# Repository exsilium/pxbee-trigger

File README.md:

# pxbee-trigger

Programmable XBee Trigger that is ZigBee Home Automation profile compliant. Possible to integrate with [SmartThings](https://www.smartthings.com) Hub v3 or a separate ZigBee / XBee network. Includes a reference hardware design up to 4 channels with a full BOM, perfect for DIYselfers out there.

Used in real life to automate garage / gate automatons.

## Hardware example

An assembled board without a mounted XBee radio. Metric scale for reference (cm.). Board dimension - 51 x 57 mm.
## Bill of Materials (BOM)

| Designator  | Component                                                                                                            | Manufacturer                                      | Quantity | SKU / Part nr.                | Spec                                                                               | Option |
| ----------- | -------------------------------------------------------------------------------------------------------------------- | ------------------------------------------------- | -------- | ----------------------------- | ---------------------------------------------------------------------------------- | ------ |
| XB1         | [Programmable XBee](https://www.digi.com/products/xbee-rf-solutions/rf-modules/xbee-zigbee#partnumbers) (with RPSMA) | [Digi](https://www.digi.com)                      |        1 | XBP24CZ7SITB003               | [PDF](http://www.digi.com/resources/documentation/digidocs/pdfs/90002002.pdf)      |        |
| BR1         | [Bridge Rectifier DF01M](https://www.mouser.ee/ProductDetail/512-DF01M)                                              | [ON Semiconductor](https://www.onsemi.com)        |        1 | Mouser No: 512-DF01M          | [PDF](https://www.mouser.ee/datasheet/2/308/DF10M-D-1803766.pdf)                   |        |
| C1 (C2)     | [Electrolytic Capacitor - Radial 220uF 50V](https://www.mouser.ee/ProductDetail/EEU-FM1H221)                         | [Panasonic](https://industrial.panasonic.com).    |      1-2 | Mouser No: 667-EEU-FM1H221.   | [PDF](https://www.mouser.ee/datasheet/2/315/ABA0000C1018-947496.pdf).              |        |
| PS1         | [DC/DC Isolated Converter Cosel MGFS1R5243R3](https://www.mouser.ee/ProductDetail/436-MGFS1R5243R3)                  | [Cosel](https://www.coseleurope.eu)               |        1 | Mouser No: 436-MGFS1R5243R3   | [PDF](https://www.mouser.ee/datasheet/2/622/SFE_MGFS-1115632.pdf)                  |        |
| Q1,Q2,Q3,Q4 | [Bipolar Transistor BC548BTA](https://www.mouser.ee/ProductDetail/512-BC548BTA)                                      | [ON Semiconductor](https://www.onsemi.com)        |        4 | Mouser No: 512-BC548BTA       | [PDF](https://www.mouser.ee/datasheet/2/308/BC548-1118644.pdf)                     |        |
| D1,D2,D3,D4 | [Diode 1N4004](https://www.mouser.ee/ProductDetail/863-1N4004RLG)                                                    | [ON Semiconductor](https://www.onsemi.com)        |        4 | Mouser No: 863-1N4004RLG      | [PDF](https://www.mouser.ee/datasheet/2/308/1N4001-D-110363.pdf)                   |        |
| K1,K2,K3,K4 | [General Purpose Relay (APAN3103)](https://www.mouser.ee/ProductDetail/769-APAN3103)                                 | [Panasonic](https://industrial.panasonic.com)     |        4 | Mouser No: 769-APAN3103       | [PDF](https://www.mouser.ee/datasheet/2/315/mech_eng_pan-1299258.pdf)              |        |
| R1,R2,R3,R4 | [Resistor RN55D1801FB14](https://www.mouser.ee/ProductDetail/71-RN55D1801FB14)                                       | [Vishay](https://www.vishay.com)                  |        4 | Mouser No: 71-RN55D1801FB14   | [PDF](https://www.mouser.ee/datasheet/2/427/cmfmil-109690.pdf)                     |        |
| XB1         | [10 pin header for XBee](https://www.mouser.ee/ProductDetail/855-M22-7131042)                                        | [Harwin](https://www.harwin.com)                  |        2 | Mouser No: 855-M22-7131042    | [PDF](https://www.mouser.ee/datasheet/2/181/M22-713-1134021.pdf)                   |        |
| J1          | [2 pin Terminal Block (PCB)](https://www.mouser.ee/ProductDetail/538-39501-1002)                                     | [Molex](https://www.molex.com)                    |        1 | Mouser No: 538-39501-1002     | [PDF](https://www.mouser.ee/datasheet/2/276/0395011002_TERMINAL_BLOCKS-163759.pdf) | A      |
|             | [2 pin Terminal Plug](https://www.mouser.ee/ProductDetail/538-39500-0002)                                            | [Molex](https://www.molex.com)                    |        1 | Mouser No: 538-39500-0002     | [PDF](https://www.mouser.ee/datasheet/2/276/0395000002_TERMINAL_BLOCKS-136229.pdf) | A      |
| J2          | [9 pin Terminal Block (PCB)](https://www.mouser.ee/ProductDetail/538-39501-1009)                                     | [Molex](https://www.molex.com)                    |        1 | Mouser No: 538-39501-1009     | [PDF](https://www.mouser.ee/datasheet/2/276/0395011009_TERMINAL_BLOCKS-163629.pdf) | A      |
|             | [9 pin Terminal Plug](https://www.mouser.ee/ProductDetail/651-1908101)                                               | [Molex](https://www.molex.com)                    |        1 | Mouser No: 651-1908101        | [PDF](https://www.mouser.ee/datasheet/2/276/0395000009_TERMINAL_BLOCKS-163669.pdf) | A      |
| J1          | [2 pin Fixed Terminal Block (PCB)](https://www.mouser.ee/ProductDetail/538-39357-0002)                               | [Molex](https://www.molex.com)                    |        1 | Mouser No: 538-39357-0002     | [PDF](https://www.mouser.ee/datasheet/2/276/0393570002_TERMINAL_BLOCKS-227759.pdf) | B      |
| J2          | [9 pin Fixed Terminal Block (PCB)](https://www.mouser.ee/ProductDetail/538-39357-0009)                               | [Molex](https://www.molex.com)                    |        1 | Mouser No: 538-39357-0009     | [PDF](https://www.mouser.ee/datasheet/2/276/0393570009_TERMINAL_BLOCKS-136250.pdf) | B      |
|             | [Antenna with RP-SMA Connector](https://www.mouser.ee/ProductDetail/712-ANT-2.4-CW-RAH)                              | [Linx Technologies](https://linxtechnologies.com) |        1 | Mouser No: 712-ANT-2.4-CW-RAH | [PDF](https://www.mouser.ee/datasheet/2/238/ant-2.4-cw-rah-ccc-1659143.pdf)        |        |
| JP1         | [6 pin Debug Header](https://www.mouser.ee/ProductDetail/538-22-28-8065)                                             | [Molex](https://www.molex.com)                    |        1 | Mouser No: 538-22-28-8065     | [PDF](https://www.mouser.ee/datasheet/2/276/0022288065_PCB_HEADERS-159204.pdf)     | O      |
| J3          | [2 pin Reset Header](https://www.mouser.ee/ProductDetail/Molex/22-28-5027)                                           | [Molex](https://www.molex.com)                    |        1 | Mouser No: 538-22-28-5027     | [PDF](https://www.mouser.ee/ProductDetail/Molex/22-28-5027)                        | O      |

Standard 3.5 width headers are used. Option **A**) uses pluggable termination; **B**) Fixed screw termination; **O**) Parts are optional and meant for development; Components can easily be switched with other termination blocks or use direct wire soldering.

## Compiling

- On 32bit Linux target, simply: `make`
- On 64bit Linux target:
    - Intall 32bit compatible libraries: `sudo apt-get install lib32stdc++6`
    - `make`
- On MacOS:
    - Install [Docker](https://www.docker.com)
    - `make builddocker`
    - `make dall`

## Firmware

- Output file: `obj/trigger.abs.bin`
- Upload the file via local XMODEM or use Over-the-air upgrade if the current firmware supports it (you can use [pxbee-fwup.js](https://github.com/exsilium/pxbee-fwup.js))
- See further [Programmable XBee documentation](http://xbee-sdk-doc.readthedocs.io)

## Trigger

Send a Unicast ZCL "On" command to trigger the connected relay for 125ms (Relay 1). The state of the switch remains in "Off" state. Broadcast command is ignored by default.

```
Endpoint: 0xEA,
clusterId: 0x0006,
profileId: 0x0104,
command: 0x01
```

## Settings

The following defines can be altered in `custom.h` prior to compilation to change the behavior how the Trigger works:

|  Name | Description | Default |
| ------| ----------- | ------- |
| `PXBEE_TRIGGER_IGNORE_BROADCAST` | When enabled, ignores broadcast commands and reacts only when unicast messages are sent to the specific address (ignores All On/All Off commands). | Enabled |
| `ZCL_MANUFACTURER` | The reported manufacturer string. For SmartThings local execution support without custom device handler, set this to "Leviton". | "PXBee" |
| `ZCL_MODEL` | The reported model string. For SmartThings local execution support without custom device handler, set this to "ZSS-10". | "Trigger" |

### Endpoints

|  Endpoint | Description |
| ----------| ----------- |
| `0xEA` | Relay 1 |
| `0xEB` | Relay 2 |
| `0xEC` | Relay 3 |
| `0xED` | Relay 4 |
| `0xEE` | Auxiliary binary input endpoint |

## License

This project is based on [exsilium/pxbee-blink-led](https://github.com/exsilium/pxbee-blink-led) boilerplate and includes the full [Digi](http://www.digi.com) XBee SDK version 1.6.0 sources.

Includes the necessary build binaries:
```
HI-CROSS+ ANSI-C Compiler for HC08 V-5.0.39, Dec 13 2011
HI-CROSS+ SmartLinker V-5.0.48, Dec 13 2011
HI-CROSS+ Burner V-5.0.16, Dec 13 2011
(c) Copyright Freescale 1987-2010
```

If not otherwise noted, the added code is [BSD licensed](LICENSE).

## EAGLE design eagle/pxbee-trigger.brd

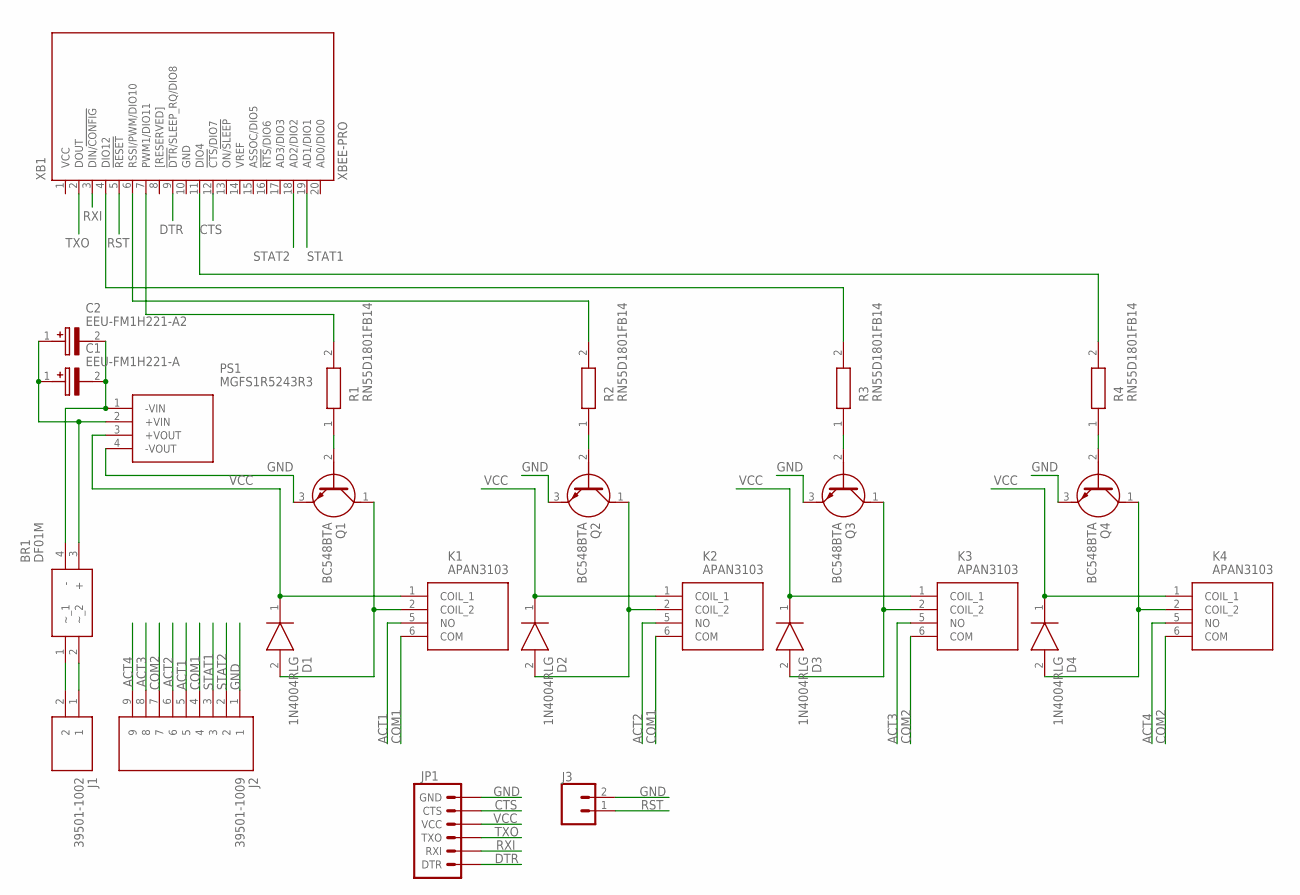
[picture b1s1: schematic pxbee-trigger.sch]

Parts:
BR1: DF01M; DIP825W114P510L828H330Q4N
C1: EEU-FM1H221-A; CAPANGLED
C2: EEU-FM1H221-A2; CAPANGLED-B
D1, D2, D3, D4: 1N4004RLG; DIOAD1405W86L465D235
J1: 39501-1002; 395011002
J2: 39501-1009; SHDR9W80P0X350_1X9_3290X690X96
J3: CONN_02; 1X02
JP1: 6_PIN_SERIAL_TARGETSILK; 6_PIN_SERIAL_TARGET_SIDE_W_SILK
K1, K2, K3, K4: APAN3103
PS1: MGFS1R5243R3; MGFS1R52415
Q1, Q2, Q3, Q4: BC548BTA
R1, R2, R3, R4: RN55D1801FB14; RESAD1526W69L610D229
XB1: XBEE-PRO

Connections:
ACT1: J2.5, K1.5 (NO)
ACT2: J2.6, K2.5 (NO)
ACT3: J2.8, K3.5 (NO)
ACT4: J2.9, K4.5 (NO)
COM1: J2.4, K1.6 (COM), K2.6 (COM)
COM2: J2.7, K3.6 (COM), K4.6 (COM)
CTS: JP1.P$5 (CTS), XB1.12 (!CTS!/DIO7)
DTR: JP1.P$1 (DTR), XB1.9 (!DTR!/SLEEP_RQ/DIO8)
GND: J2.1, J3.2, JP1.P$6 (GND), PS1.4 (-VOUT), Q1.3 (E), Q2.3 (E), Q3.3 (E), Q4.3 (E), XB1.10 (GND)
unnamed: Q1.2 (B), R1.1
unnamed: Q2.2 (B), R2.1
unnamed: D1.2 (A), K1.2 (COIL_2), Q1.1 (C)
unnamed: D2.2 (A), K2.2 (COIL_2), Q2.1 (C)
unnamed: Q3.2 (B), R3.1
unnamed: D3.2 (A), K3.2 (COIL_2), Q3.1 (C)
unnamed: Q4.2 (B), R4.1
unnamed: BR1.1 (~_1), J1.2
unnamed: BR1.2 (~_2), J1.1
unnamed: D4.2 (A), K4.2 (COIL_2), Q4.1 (C)
unnamed: R1.2, XB1.7 (PWM1/DIO11)
unnamed: R2.2, XB1.6 (RSSI/PWM/DIO10)
unnamed: R3.2, XB1.4 (DIO12)
unnamed: R4.2, XB1.11 (DIO4)
RST: J3.1, XB1.5 (!RESET)
RXI: JP1.P$3 (RXI), XB1.3 (DIN/!CONFIG)
STAT1: J2.3, XB1.19 (AD1/DIO1)
STAT2: J2.2, XB1.18 (AD2/DIO2)
TXO: JP1.P$2 (TXO), XB1.2 (DOUT)
VCC: D1.1 (K), D2.1 (K), D3.1 (K), D4.1 (K), JP1.P$4 (VCC), K1.1 (COIL_1), K2.1 (COIL_1), K3.1 (COIL_1), K4.1 (COIL_1), PS1.3 (+VOUT), XB1.1 (VCC)
VIN+: BR1.3 (+), C1.1 (+), C2.1 (+), PS1.2 (+VIN)
VIN-: BR1.4 (-), C1.2 (-), C2.2 (-), PS1.1 (-VIN)

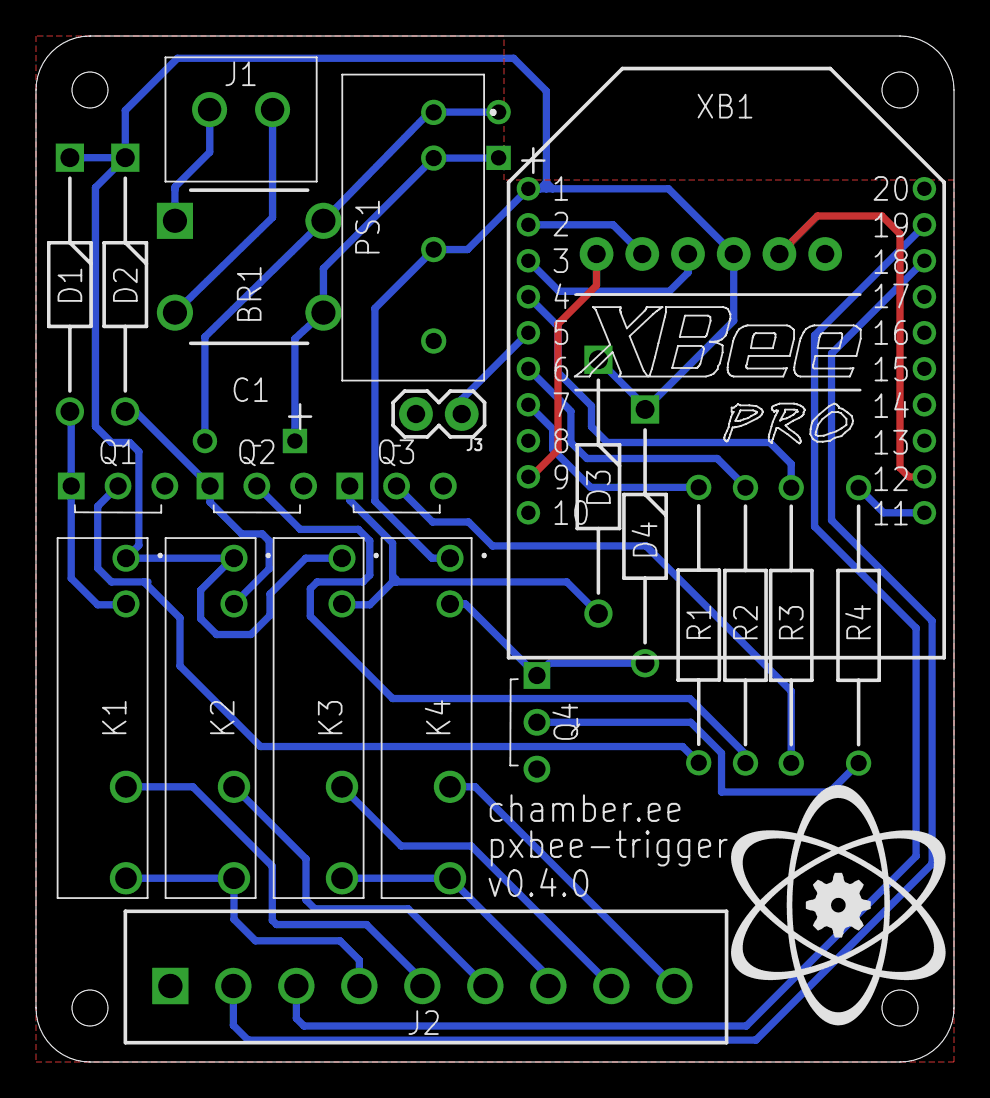
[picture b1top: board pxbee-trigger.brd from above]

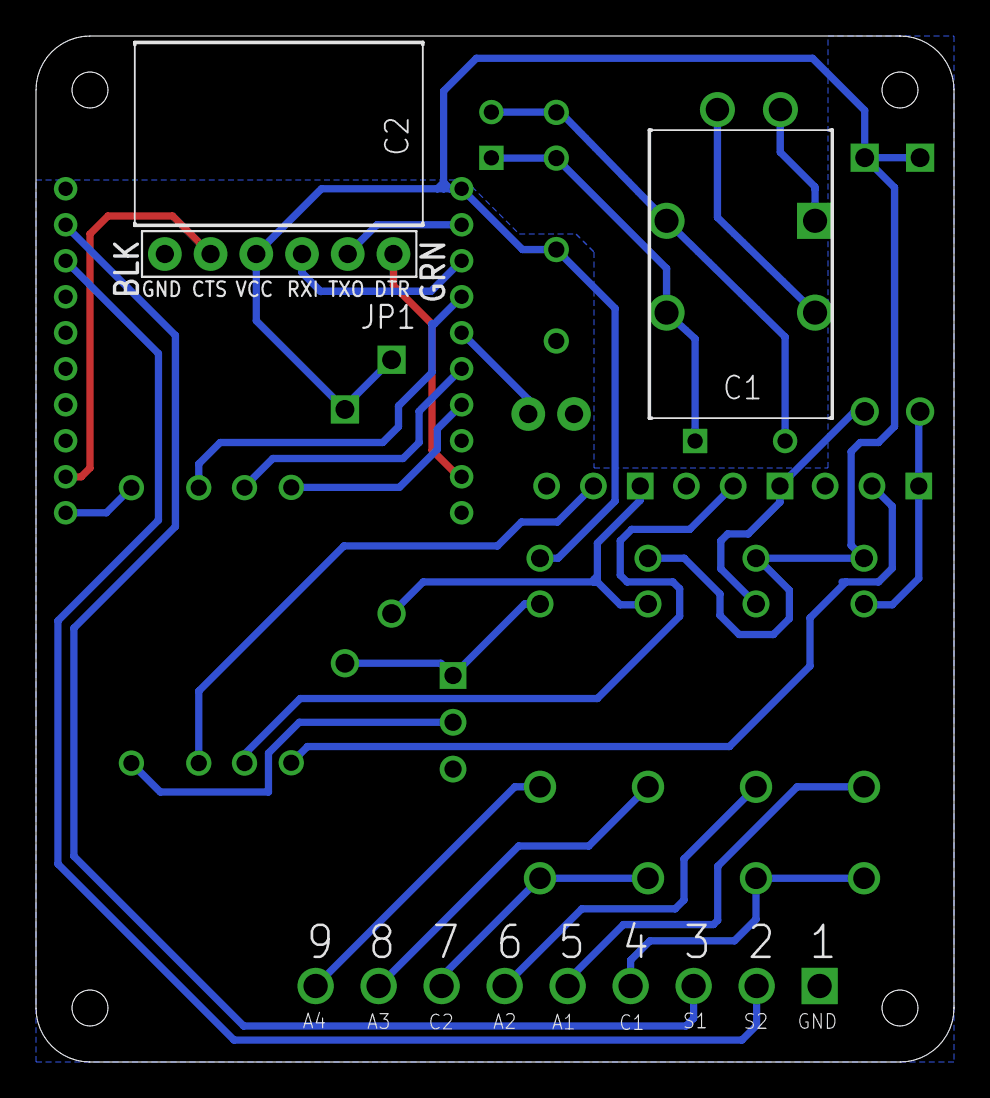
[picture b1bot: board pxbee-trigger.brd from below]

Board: 2 copper layers, 51.0 x 57.0 mm, 25 parts (3 on the bottom side), 31 nets.

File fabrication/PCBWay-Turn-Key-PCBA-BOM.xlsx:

|  |  | PXBee-Trigger PCBA BOM
Item # | *Designator | *Qty | Manufacturer | *Mfg Part # | Description / Value | *Package/Footprint | Type | Your Instructions / Notes
1 | BR1 | 1 | ON Semiconductor | DF01M | Bridge Rectifiers 1.5A Bridge | PDIP-4 | Thru-hole
2 | C1 | 1 | Panasonic | EEU-FM1H221 | Aluminium Electrolytic Capacitors - Radial Leaded 220UF 50V ELECT FM RADIAL | Radial 10mm | Thru-hole | Placement on top! Needs to be mounted higher and with 90 degree angle locating 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
3 | PS1 | 1 | Cosel | MGFS1R5243R3 | Isolated DC/DC Converters 1.32W 9-36Vin 3.3V 0.4A PCB SIP6 | 17.0X12.0X8.5mm | Thru-hole
4 | Q1,Q2,Q3,Q4 | 4 | ON Semiconductor | BC548BTA | Bipolar Transistors - BJT NPN 30V 100mA HFE/450 | TO-92-3 Kinked Lead | Thru-hole
5 | D1,D2,D3,D4 | 4 | ON Semiconductor | 1N4004RLG | Rectifiers 400V 1A Standard | DO-41 | Thru-hole
6 | K1,K2,K3,K4 | 4 | Panasonic | APAN3103 | General Purpose Relays 3.0volts 1 Form A PLC Relay | 5.0X20.0X12.5mm | Thru-hole
7 | R1,R2,R3,R4 | 4 | Vishay | RN55D1801FB14 | Metal Film Resistors - Through Hole 1/8watt 1.8Kohms 1% 100ppm | B14 | Thru-hole
8 | XB1 (Left, Right) | 2 | Harwin | M22-7131042 | Headers & Wire Housings 10 PIN SIL VERTICAL GOLD+TIN SOCKET | 10POS | Thru-hole | 2mm pitch
9 | J1 | 1 | Molex | 39357-0002 | Fixed Terminal Blocks 3.5MM FIXED PCB 2P 16-26AWG | 2POS | Thru-hole
10 | J2 | 1 | Molex | 39357-0009 | Fixed Terminal Blocks 3.5MM FIXED PCB 9P 16-26AWG | 9POS | Thru-hole
11 | J3 | 1 | Molex | 22-28-5027 | Headers & Wire Housings KK 100 Hdr Assy Bkwy Bkwy 02 Ckt 30 SGold | 2POS | Thru-hole
12 | JP1 | 1 | Molex | 22-28-8065 | Headers & Wire Housings KK 100 Hdr Assy RA B Bkwy 06 Ckt 30 SGold | 6POS | Thru-hole | Placement on bottom side

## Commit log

2016-09-15 Bootstrapping from pxbee-blink-led (d77c995)
2016-09-15 RELAY and relayTimer components added; naming
    - Project target renamed to trigger
2016-09-27 Blink led/relay on teh Grove Xbee Carrier
2016-10-02 Custom endpoint, profile and cluster
    - Playing with the TPM1 timer
2016-10-03 ZDO Endpoint added
2016-10-12 Untabify and trigger() function
2016-10-16 Syntax error fix, relayTimer now actually turns of the relay
2016-10-16 Short readme added with BOM and instructions for use
2017-07-02 Non-working progress commit
    - Changing to 0x0104 Profile (HA)
    - Ability to debug messages sent by ST
    - Application version request reply working
2017-07-04 More proper Simple descriptor handling
    - Answering all the ZCL requests that ST sends
2017-07-04 Refactoring for some niceties
    - Print operating PAN ID
    - Init additional radio settings
    - Adding debug output to 0x0006 cluster handler
2017-07-04 Missing structure for ZCL state keeping
    Fixing the missing structure global
2017-07-04 Majority of the signalling is now operational
    - Turning on / Turning off state still gets stuck
2017-07-05 Readme update
2017-07-06 Reporting back proper state changes
    For Smartthings mobile GUI to operate properly, both the On state and Off state changes must be reported back
    - Report back On state
    - wait one second
    - Report back Off state
2017-07-06 Removing thew frame_control magic number
2017-10-25 Ignore broadcast command
    - Closes #2, Ignore broadcast command by default
    - Version string bump to v0.1.0
    - Ready to be merged to master
2017-10-25 Only unicast command is accepted
2018-01-01 Additional settings should set API mode to non-escaping
    - ZigBee HA AP needs to be 1 (non-escaped) (based on Digi knowledge-base article). Original issue reported by ST community member gazor
    - Added err.txt to ignore list
2018-01-18 WIP: Improvements to structure, support for SmartThings local processing
    - custom_ep_default_cluster() has been renamed to custom_ep_basic_cluster() because naming matters and it's about handling the ZigBee basic cluster comms
    - custom_ep_rx_cluster() -> custom_ep_rx_on_off_cluster()
    - new custom_ep_rx_notimpl_cluster()
    - Reports new nonimplemented clusters as capability (0003,0004,0005)
    - Utility function for easier string manipulation, thanks ST member @gazor!
    - LICENSE added for clarity
2018-01-20 Additional comments added and readme update
    - Clarification on how to join the device as a switch without custom device handler in SmartThings by reporting itself as Leviton / ZSS-10 device
2018-01-20 Adding link to the pxbee-fwup.js project
    - Clarification on tooling options for uploading the firmware via XMODEM
2020-01-07 4 channel relay PCB design sent in for fabrication
    - First version for prototyping
    - Autodesk Eagle backup files added to gitignore
2020-01-17 Change of connector elements, smaller dimensions
    - Change from Phoenix contact to 3.5mm step Molex Eurotype connectors
    - Dimension the board to fit inside a small plastic conjunction box 75x75mm
    - Still work in progress (WIP)
    - Addresses fabrication remarks in #5
2020-01-17 Board routed; Updated parts library
    - Freed pin 20, using pin 4 for gate/door status input
    - Addresses findings in #5
2020-01-17 One airwire network detected; brd corners chopped
    - Addresses findings in #5
2020-01-23 Board dimension changes
    - Dimensioned to 75x75mm
    - 9 pin terminal block used to gain one more status pin
    - Parts library updated (removed unused parts, added new ones)
    - Addresses findings in #5
2020-02-04 PCB Board changes
    - Ready for fabrication v0.1.2-pcbfab.1
    - Addresses findings in #5
    - New pin assignment from XBee side to accommodate GPIO interrupt usage
2020-02-21 Initial commit to support multiple endpoints and relays
    This is a work in progress to support new design with multiple relay channels.
2020-03-27 Shrinking the pcb design to 51x64mm
    - Addressing findings in #6
    - Eagle upgrade to 9.6.0
    - WIP
2020-03-27 Further shrinkin the pcb size, new format: 51x57mm
    - Addresses findings in #6
2020-03-27 PCB layout fine tuning and fabrication prep
    - Addresses findings in #6
2020-06-05 By default wrap the toolchain in docker executable
2020-06-05 Added startup check for STATUS pin states
2020-06-12 Optimized printf usage
    - During experimentation ran into issue of exhausting APP_ROM space. The overuse of printf is contributing to the problem.
    - Relies more on hex_dump() and puts()
2020-06-15 Adding initial handling for Binary Input cluster
2020-06-18 Binary Input cluster read attribute; improvements
    - Relays are all reset on timer experitation
    - On/cluster handles multiple endpoints
    - MFG Specific flags removed
    - Bug fixes
2020-06-30 Change in irq logic for status pins; relay_2 fixed
    - The realisation that the interrupt is and can only be configured one way (Edge fall). We start a periodic timer to detect returning to normal state.
    - Relay 2 was not functioning correctly because the pin configuration was incorrectly set as input
2020-06-30 Debug output added for contact open (status_2 pin)
2020-07-17 Set WRAPINDOCKER env for Github Action
2020-07-17 Update BOM, fixes #9
2020-07-30 Added capacitors for fixing #12
    - Version of the PCB updated to v0.3.0
2020-07-30 UART header added for easier debugging
    - Fixes #13
2020-07-30 Change CTS routing on PCB
    - Further contributes to #13
2020-07-30 Gerber files updated for fabrication
2021-03-19 Bridge rectifier upgrade; XBee reset header
    - [Parts] Bridge rectifier upgraded from DF005 to DF01, previous part was underdimensioned
    - [SCH,BRD] Added J3 pinout for XBee Reset
    - [BRD] Version bumped to v0.4.0
2021-03-25 POM update
    - Added capacitor
    - Upgraded Bridge Rectifier
2021-03-25 Add serialpass mode, main menu change, status pins
    - Serialpass mode that can be easily accessed with the S option’
    - Removal of B (sysapp banner) from the main menu as it clashes with the Bypass shortcut from the bootloader menu (easier for debbugging purposes)
    - Swapped the status pins as in the physical design, order changes
2021-03-26 Docker build environment upgrade to Focal Fossa
2021-04-26 Status pin corrected in comment
2021-05-03 Fix comment on pin assignment for status pins
2021-05-04 Support for GPIO_IRQ_EDGE_BOTH interrupt type - Allow gpio configuration with edge value of 2 (0b10) - Extend kbiedg parameters to uint16 to keep 2 bits per interrupt slot - Call ISR on both slopes w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
2021-06-01 Improved status pin logic - New implementation around BOTH edge ISR #15 - Watchdog resets added to limit triggering - Fixes #14
2021-06-01 BOM update for optional dev parts
2021-06-29 Minor changes to BRD; PCBA BOM; Gerber updates
    - Minor parts and silkscreen modifications for cleanup
    - Added PCBWay PCBA Bom for turnkey solution quote #17
    - Cam processed gerber fabrication files for v0.4.0 version of the board
2021-06-30 Added designator to the BOM list
2021-08-12 Add mounting file #17
2021-08-12 Update to main README
    - Added reference hardware picture
    - Reduced the role of SmartThings as it’s not a major integration point going forward
    - Endpoints described
2021-08-12 App version changed to v0.4.0-rc.0
    - This allows a pre-release to happen
2021-09-16 Comments on mapping endpoints with relays

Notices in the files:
parts and their libraries:
SparkFun-Connectors: Licensing: Creative Commons ShareAlike 4.0 International - https://creativecommons.org/licenses/by-sa/4.0
